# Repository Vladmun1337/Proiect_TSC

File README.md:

# Proiect TSC - Openbook e-book reader

Project link: https://ocw.cs.pub.ro/courses/tsc/proiect2025

## Introduction

For this project, I have implemented an open source e-book reader using ***Autodesk Fusion360***.
The architecture is based on an ESP32-C6 low power microcontroller (+ Wi-Fi & Bluetooth).

The display is using e-paper ink. The project supports micro SD reading through the specialized
interface and USB type C charging for a Polymer Lithium-Ion battery, prioritizing performance
and efficient power consumption.

## Diagram

## Contents

```
- hardware      -> .brd and .sch files of the board
- mechanical    -> .zip files of project's 3D models (standard and exploded view)
- Manufacturing -> Bill of Materials (BOM), Pick and Place (PnP), Gerber files (.zip)
- images        -> Snapshots of project
- LICENSE
- README.md
```

## Implementation & Workflow

1. **Implementation of the schematic**: The deskassistant library, offered by the lecture, was used. All components placed, linked and tagged
   for easier workflow in the PCB part.
2. **PCB**: Board was trimmed to fit specifications and accomodate busses. Components were then placed, respecting the DRC constraints file and routed
accordingly. Power(0.3mm) and data(0.15mm) lines were routed with different gauges and power routing was done mostly on top layer.
3. **3D Modelling**: All components were researched online and their specific 3D model was imported in the library. For a better grasp of the components used,
check BOM below. After the PCB was succesfully modelled, a battery and e-paper display were sketched from scratch.
4. **Fitting everything**: PCB, battery and display were fitted inside the given encasing and given a photoshoot. :-)

## Bill of Materials (with links)

| Name                                             | Link                                                                 | Datasheet                                                            |
|--------------------------------------------------|----------------------------------------------------------------------|----------------------------------------------------------------------|
| 112A-TAAR-R03                                    | [Link](https://store.comet.srl.ro/Catalogue/Product/43497/)         | [Datasheet](https://store.comet.bg/download-file.php?id=27596)      |
| 744043680                                  | [Link](https://eu.mouser.com/ProductDetail/Wurth-Elektronik/744043680?qs=PGXP4M47uW6VkZq%252BkzjrHA%3D%3D) | [Datasheet](https://www.we-online.com/components/products/datasheet/744043680.pdf) |
| BD5229G-TR                                       | [Link](https://componentsearchengine.com/part-view/BD5229G-TR/ROHM%20Semiconductor) | [Datasheet](https://datasheet.datasheetarchive.com/originals/distributors/Datasheets_SAMA/f2b9741ef86007909f138d561a359946.pdf) |
| Button                                           | [Link](https://industry.panasonic.com/global/en/products/control/switch/light-touch/number/evqpuj02k) | [Datasheet](https://industry.panasonic.com/global/en/downloads?tab=catalog&small_g_cd=203&part_no=EVQPUJ02K&q=RVZRUFVKMDJLJTdDMTMlN0MyMDMlN0MzNDU5JTdDMSU3QyU3QzIlN0M%3D) |
| Capacitor                                   | [Link](https://componentsearchengine.com/part-view/CC0402MRX5R5BB106/YAGEO) | [Datasheet](https://componentsearchengine.com/Datasheets/2/CC0402MRX5R5BB106.pdf) |
| CPH3225A                                         | [Link](https://www.snapeda.com/parts/CPH3225A/Seiko+Instruments/view-part/?ref=eda) | [Datasheet](https://www.snapeda.com/parts/CPH3225A/Seiko%20Instruments/datasheet/) |
| DS3231SN RTC                                     | [Link](https://www.snapeda.com/parts/DS3231SN%23/Analog+Devices/view-part/?ref=eda) | [Datasheet](https://www.snapeda.com/parts/DS3231SN%23/Analog%20Devices/datasheet/) |
| ESP32 WROVER 0805 Capacitor                      | [Link](https://ro.mouser.com/ProductDetail/KYOCERA-AVX/SD0805S020S1R0?qs=jCA%252BPfw4LHbpkAoSnwrdjw%3D%3D) | [Datasheet](https://ro.mouser.com/datasheet/2/40/schottky-3165252.pdf) |
| ESP32 WROVER BME680 Sensor                       | [Link](https://www.snapeda.com/parts/BME680/Bosch/view-part/?welcome=home) | [Datasheet](https://www.snapeda.com/parts/BME680/Bosch%20Sensortec/datasheet/) |
| ESP32 WROVER MCP73831           | [Link](https://eu.mouser.com/ProductDetail/Microchip-Technology/MCP73831T-2ACI-OT?qs=yUQqVecv4qvbBQBGbHx0Mw%3D%3D) | [Datasheet](https://eu.mouser.com/datasheet/2/268/MCP73831_Family_Data_Sheet_DS20001984H-3441711.pdf) |
| ESP32 WROVER P-Channel MOSFET                    | [Link](https://componentsearchengine.com/part-view/DMG2305UX-7/Diodes%20Incorporated) | [Datasheet](https://www.diodes.com//assets/Datasheets/DMG2305UX.pdf) |
| ESP32-C6 WROOM-1-N8                              | [Link](https://www.snapeda.com/parts/ESP32-C6-WROOM-1-N8/Espressif+Systems/view-part/?ref=eda) | [Datasheet](https://www.snapeda.com/parts/ESP32-C6-WROOM-1-N8/Espressif%20Systems/datasheet/) |
| ESP32C6 Varistor 1812                            | [Link](https://ro.mouser.com/ProductDetail/EPCOS-TDK/B72520T0350K062?qs=dEfas%2FXlABIszF52uu7vrg%3D%3D) | [Datasheet](https://www.tdk-electronics.tdk.com/inf/75/db/CTVS_14/Surge_protection_series.pdf) |
| FH34SRJ-24S-0.5SH Connector                      | [Link](https://componentsearchengine.com/part-view/FH34SRJ-24S-0.5SH(99)/Hirose) | [Datasheet](https://www.hirose.com/en/product/document?clcode=CL0580-1255-6-99&productname=FH34SRJ-24S-0.5SH(99)&series=FH34SRJ&documenttype=2DDrawing&lang=en&documentid=0000990903) |
| LED 0603                                    | [Link](https://www.snapeda.com/parts/KP-1608SURCK/Kingbright/view-part/?ref=search&t=LED%200603) | [Datasheet](https://www.snapeda.com/parts/KP-1608SURCK/Kingbright/datasheet/) |
| LTSPICE Resistor 0402                            | [Link](https://componentsearchengine.com/part-view/R0402%201%25%20100%20K%20(RC0402FR-07100KL)/YAGEO) | [Datasheet](https://www.yageo.com/upload/media/product/products/datasheet/rchip/PYu-RC_Group_51_RoHS_L_12.pdf) |
| MAX17048G+T10                 | [Link](https://www.snapeda.com/parts/MAX17048G+T10/Analog+Devices/view-part/?ref=eda) | [Datasheet](https://www.snapeda.com/parts/MAX17048G+T10/Analog%20Devices/datasheet/) |
| MBR0530 Schottky                           | [Link](https://www.snapeda.com/parts/MBR0530/Onsemi/view-part/?ref=eda) | [Datasheet](https://www.snapeda.com/parts/MBR0530/ON%20Semiconductor/datasheet/) |
| PGB1010603MR                            | [Link](https://www.snapeda.com/parts/PGB1010603MR/Littelfuse/view-part/?ref=eda) | [Datasheet](https://www.snapeda.com/parts/PGB1010603MR/Littelfuse%20Inc./datasheet/) |
| QWIIC Connector                                  | [Link](https://eu.mouser.com/ProductDetail/Adafruit/4208?qs=PzGy0jfpSMtbScLbr0L5dw%3D%3D) | [Datasheet](https://www.youtube.com/watch?v=dQw4w9WgXcQ) |
| RCL CPOL 3528                                    | [Link](https://www.snapeda.com/parts/TAJB475K025RNJ/AVX/view-part/?ref=dk&t=capacitor%203528&con_ref=None) | [Datasheet](https://s3.amazonaws.com/snapeda/datasheet/TAJB475K025RNJ_AVX.pdf) |
| SI1308EDL-T1-GE3 MOSFET                          | [Link](https://www.snapeda.com/parts/SI1308EDL-T1-GE3/Vishay+Siliconix/view-part/?ref=eda) | [Datasheet](https://www.youtube.com/watch?v=dQw4w9WgXcQ) |
| SJ                                               | [Link](https://grabcad.com/library/solder-jumpers-1)                 | [Datasheet](https://www.youtube.com/watch?v=dQw4w9WgXcQ)             |
| TPTP20R                                          | [Link](https://easyeda.com/component/7524403feb2642ac9f9f26dfb93ceacf) | [Datasheet](https://easyeda.com/component/7524403feb2642ac9f9f26dfb93ceacf) |
| USB4110-GF-A USB                             | [Link](https://componentsearchengine.com/part-view/USB4110-GF-A/GCT%20(GLOBAL%20CONNECTOR%20TECHNOLOGY)) | [Datasheet](https://gct.co/files/drawings/usb4110.pdf)             |
| USBLC6-2SC6Y USB                | [Link](https://www.snapeda.com/parts/USBLC6-2SC6Y/STMicroelectronics/view-part/?ref=eda) | [Datasheet](https://www.snapeda.com/parts/USBLC6-2SC6Y/STMicroelectronics/datasheet/) |
| W25Q512JVEIQ Flash                      | [Link](https://www.snapeda.com/parts/W25Q512JVEIQ/Winbond+Electronics/view-part/?ref=eda) | [Datasheet](https://www.snapeda.com/parts/W25Q512JVEIQ/Winbond%20Electronics/datasheet/) |
| XC6220A331MR-G Voltage Regulator                 | [Link](https://componentsearchengine.com/part-view/XC6220A331MR-G/Torex) | [Datasheet](https://product.torexsemi.com/system/files/series/xc6220.pdf) |

## ESP32-C6 Pinout

An overview of how the ESP32-C6 pins are assigned within the system, grouped by function.

### Power
- **3V3 (Pin 2 & Top Right):** 3.3V supply for ESP32 and peripherals.
- **GND (Bottom Right):** Common ground.

### Boot and Reset
- **GPIO8 (Pin 15):** Boot mode selection, pulled low via 10KΩ.
- **RESET (Pin 3):** Manual reset input.

### SPI (E-Paper Display, SD Card, Flash)
- **MISO (Pin 27)**
- **MOSI (Pin 10)**
- **SCK (Pin 7)**
- **SS_SD (Pin 4):** Chip Select for SD card or other SPI device.
- **EPD_CS (Pin 11):** Chip Select for E-Paper Display.
- **FLASH_CS (Pin 12):** Chip Select for NOR Flash.

### E-Paper Display Control
- **EPD_BUSY (Pin 26)**
- **EPD_DC (Pin 5)**
- **EPD_RST (Pin 21)**
- **EPD_3V3_C (Pin 19):** Likely power enable/control.

### I2C (RTC & Sensors)
- **SDA (Pin 20)**
- **SCL (Pin 21)**
- **I2C_PW (Pin 18):** Power enable for I2C devices.
- **INT_RTC (Pin 8):** RTC interrupt.
- **RTC_RST (Pin 16)**

### USB
- **USB_D- (Pin 13)**
- **USB_D+ (Pin 14)**

### UART
- **TX (Pin 25)**
- **RX (Pin 24)**

### Other GPIO
- **IO_CHANGE (Pin 23):** Interrupt or status input/output.

## Total Power Consumption Overview

In a typical operating scenario—where the ESP32-C6 remains active with Wi-Fi enabled, the e-paper display refreshes every 10 seconds, and the BME688 sensor continuously collects environmental data—the estimated current draw for the system is as follows:

| Component                          | Estimated Consumption (mA) |
|-----------------------------------|-----------------------------|
| ESP32-C6 (Wi-Fi enabled)          | 200 mA                      |
| E-Paper Display (during update)   | 40 mA                       |
| BME688 Sensor (continuous use)    | 2 mA                        |
| Real-Time Clock (RTC) Module      | 2 mA                        |
| SD Card (active use)              | 12 mA                       |
| External NOR Flash Memory         | 25 mA                       |

### Typical Total Current Draw

**Total: 281 mA**

This estimate represents a high-activity configuration. In lower-power modes (e.g., sleep or deep sleep), consumption can be significantly reduced.

## Conclusions

This project was very exciting for me. A lot of difficulties came from me having little to no prior experience with the autodesk suite, but everything sorted
itself out. I feel that I could get a good grasp of what working in the hardware and product industry means and am open to work on more other such projects! :-)

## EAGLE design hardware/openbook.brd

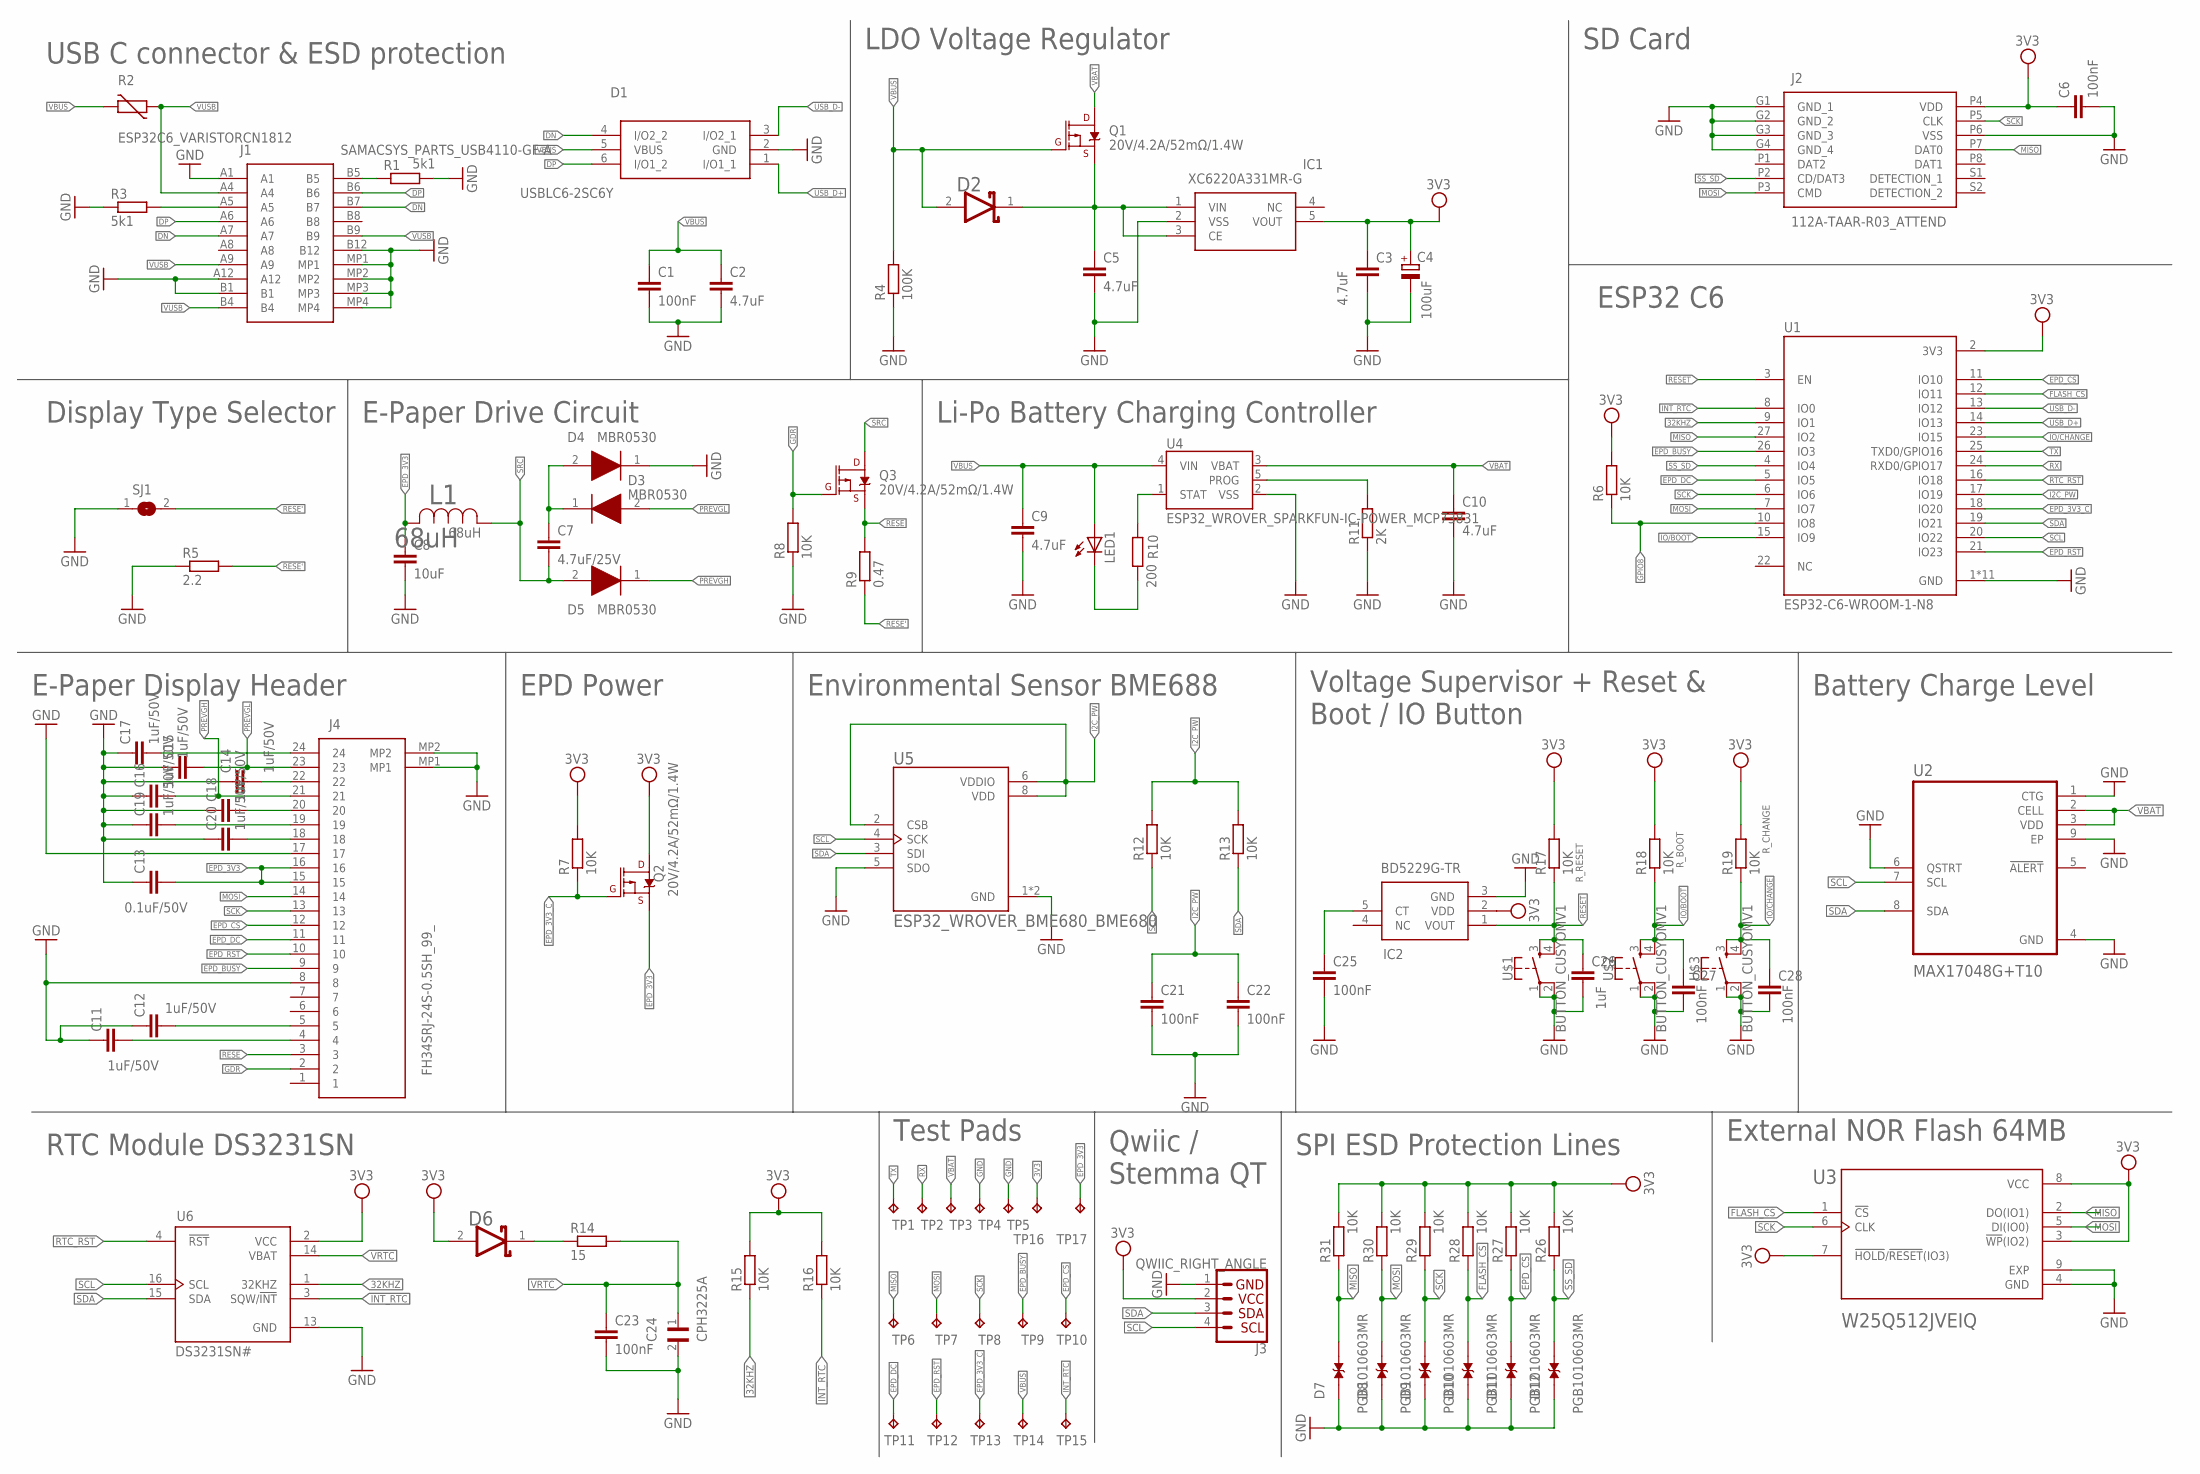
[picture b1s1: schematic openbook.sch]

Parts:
C1, C6, C21, C22, C23, C25, C27, C28: 100nF; EAGLE-LTSPICE_C0402
C2, C3, C5, C9, C10: 4.7uF; EAGLE-LTSPICE_C0402
C4: 100uF; RCL_CT3528
C7: 4.7uF/25V; EAGLE-LTSPICE_C0402
C8: 10uF; EAGLE-LTSPICE_C0402
C11, C12, C14, C15, C16, C17, C18, C19, C20: 1uF/50V; EAGLE-LTSPICE_C0402
C13: 0.1uF/50V; EAGLE-LTSPICE_C0402
C24: CPH3225A; CAPCP3225X100N
C26: 1uF; EAGLE-LTSPICE_C0402
D1: USBLC6-2SC6Y; SOT95P280X145-6N
D2, D6: ESP32_WROVER_AVX---SD0805S020S1R0_AVX_SD0805S020S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; ESP32_WROVER_AVX---SD0805S020S1R0_AVX_SD0805S020S1R0_0
D3, D4, D5: MBR0530; SOD3716X135N
D7, D8, D9, D10, D11, D12: PGB1010603MR; DIOC1608X36N
IC1: XC6220A331MR-G; SOT95P280X120-5N
IC2: BD5229G-TR; SOT95P280X125-5N
J1: SAMACSYS_PARTS_USB4110-GF-A; SAMACSYS_PARTS_USB4110GFA
J2: 112A-TAAR-R03_ATTEND; 112ATAARR03ATTEND
J3: QWIIC_RIGHT_ANGLE; JST04_1MM_RA
J4: FH34SRJ-24S-0.5SH_99_; FH34SRJ24S05SH99
L1: 68uH; IND_4828-WE-TPC_WRE
LED1: ADAFRUIT_LEDCHIP-LED0603; ADAFRUIT_CHIP-LED0603
Q1, Q2, Q3: 20V/4.2A/52mΩ/1.4W; ESP32_WROVER_SPARKFUN-DISCRETESEMI_SOT23-3
R1, R3: 5k1; ESP32_WROVER_EAGLE-LTSPICE_R0402
R2: ESP32C6_VARISTORCN1812; ESP32C6_VARISTOR_CT/CN1812
R4: 100K; ESP32_WROVER_EAGLE-LTSPICE_R0402
R5: 2.2; ESP32_WROVER_EAGLE-LTSPICE_R0402
R6, R7, R8, R12, R13, R15, R16, R17, R18, R19, R26, R27, R28, R29, R30, R31: 10K; ESP32_WROVER_EAGLE-LTSPICE_R0402
R9: 0.47; ESP32_WROVER_EAGLE-LTSPICE_R0402
R10: 200; ESP32_WROVER_EAGLE-LTSPICE_R0402
R11: 2K; ESP32_WROVER_EAGLE-LTSPICE_R0402
R14: 15; ESP32_WROVER_EAGLE-LTSPICE_R0402
SJ1: SJ
TP1, TP2, TP3, TP4, TP5, TP6, TP7, TP8, TP9, TP10, TP11, TP12, TP13, TP14, TP15, TP16, TP17: TPTP20R; TP20R
U1: ESP32-C6-WROOM-1-N8; XCVR_ESP32-C6-WROOM-1-N8
U2: MAX17048G+T10; SON50P200X200X80-9N
U3: W25Q512JVEIQ; SON127P600X800X80-9N
U4: ESP32_WROVER_SPARKFUN-IC-POWER_MCP73831; ESP32_WROVER_SPARKFUN-IC-POWER_SOT23-5
U5: ESP32_WROVER_BME680_BME680; ESP32_WROVER_BME680_PSON80P300X300X100-8N
U6: DS3231SN#; SOIC127P1032X265-16N
U$1, U$2, U$3: BUTTON_CUSYOMV1; MYBUTTON

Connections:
3V3: C3.1, C4.+, C6.1, D6.2 (ANODE), IC1.5 (VOUT), IC2.2 (VDD), J2.P4 (VDD), J3.2, Q2.3 (D), R6.2, R7.2, R15.2, R16.2, R17.2, R18.2, R19.2, R26.2, R27.2, R28.2, R29.2, R30.2, R31.2, TP16.TP, U1.2 (3V3), U3.3 (!WP!(IO2)), U3.7 (!HOLD!/!RESET!(IO3)), U3.8 (VCC), U6.2 (VCC)
32KHZ: R15.1, U1.9 (IO1), U6.1 (32KHZ)
DN: D1.4 (I/O2_2), J1.A7, J1.B7
DP: D1.6 (I/O1_2), J1.A6, J1.B6
EPD_3V3: C8.1, C13.2, J4.15, J4.16, L1.2, Q2.2 (S), TP17.TP
EPD_3V3_C: Q2.1 (G), R7.1, TP13.TP, U1.18 (IO20)
EPD_BUSY: J4.9, TP9.TP, U1.26 (IO3)
EPD_CS: D11.2, J4.12, R27.1, TP10.TP, U1.11 (IO10)
EPD_DC: J4.11, TP11.TP, U1.5 (IO5)
EPD_RST: J4.10, TP12.TP, U1.21 (IO23)
FLASH_CS: D10.2, R28.1, U1.12 (IO11), U3.1 (!CS)
GDR: J4.2, Q3.1 (G), R8.2
GND: C1.2, C2.2, C3.2, C4.-, C5.2, C6.2, C8.2, C9.2, C10.2, C11.1, C12.1, C13.1, C14.1, C15.1, C16.1, C17.1, C18.1, C19.1, C20.1, C21.2, C22.2, C23.2, C24.2, C25.2, C26.2, C27.2, C28.2, D1.2 (GND), D4.1 (K), D7.1, D8.1, D9.1, D10.1, D11.1, D12.1, IC1.2 (VSS), IC2.3 (GND), J1.A1, J1.A12, J1.B1, J1.B12, J1.MP1, J1.MP2, J1.MP3, J1.MP4, J2.G1 (GND_1), J2.G2 (GND_2), J2.G3 (GND_3), J2.G4 (GND_4), J2.P6 (VSS), J3.1, J4.8, J4.17, J4.MP1, J4.MP2, R1.2, R3.1, R4.1, R5.1, R8.1, R11.1, SJ1.1, TP4.TP, TP5.TP, U1.1 (GND), U1.28 (GND), U1.29_1 (GND), U1.29_2 (GND), U1.29_3 (GND), U1.29_4 (GND), U1.29_5 (GND), U1.29_6 (GND), U1.29_7 (GND), U1.29_8 (GND), U1.29_9 (GND), U2.1 (CTG), U2.4 (GND), U2.6 (QSTRT), U2.9 (EP), U3.4 (GND), U3.9 (EXP), U4.2 (VSS), U5.1 (GND), U5.5 (SDO), U5.7 (GND), U6.13 (GND), U$1.1, U$1.2, U$2.1, U$2.2, U$3.1, U$3.2
GPIO8: R6.1, U1.10 (IO8)
I2C_PW: C21.1, C22.1, R12.2, R13.2, U1.17 (IO19), U5.2 (CSB), U5.6 (VDDIO), U5.8 (VDD)
INT_RTC: R16.1, TP15.TP, U1.8 (IO0), U6.3 (SQW/!INT)
IO/BOOT: C27.1, R18.1, U1.15 (IO9), U$2.3, U$2.4
IO/CHANGE: C28.1, R19.1, U1.23 (IO15), U$3.3, U$3.4
MISO: D7.2, J2.P7 (DAT0), R31.1, TP6.TP, U1.27 (IO2), U3.2 (DO(IO1))
MOSI: D8.2, J2.P3 (CMD), J4.14, R30.1, TP7.TP, U1.7 (IO7), U3.5 (DI(IO0))
unnamed: D6.1 (CATHODE), R14.1
unnamed: J1.B5, R1.1
unnamed: J1.A5, R3.2
unnamed: C5.1, D2.1 (CATHODE), IC1.1 (VIN), IC1.3 (CE), Q1.2 (S)
unnamed: C7.1, D3.1 (K), D4.2 (A)
unnamed: LED1.C, R10.1
unnamed: R10.2, U4.1 (STAT)
unnamed: R11.2, U4.5 (PROG)
unnamed: C11.2, J4.4
unnamed: C12.2, J4.5
unnamed: C20.2, J4.18
unnamed: C19.2, J4.19
unnamed: C18.2, J4.20
unnamed: C14.2, J4.22
unnamed: C17.2, J4.24
unnamed: C25.1, IC2.5 (CT)
PREVGH: C16.2, D5.1 (K), J4.21
PREVGL: C15.2, D3.2 (A), J4.23
RESE: J4.3, Q3.2 (S), R9.2
RESE': R5.2, R9.1, SJ1.2
RESET: C26.1, IC2.1 (VOUT), R17.1, U1.3 (EN), U$1.3, U$1.4
RTC_RST: U1.16 (IO18), U6.4 (!RST)
RX: TP2.TP, U1.24 (RXD0/GPIO17)
SCK: D9.2, J2.P5 (CLK), J4.13, R29.1, TP8.TP, U1.6 (IO6), U3.6 (CLK)
SCL: J3.4, R12.1, U1.20 (IO22), U2.7 (SCL), U5.4 (SCK), U6.16 (SCL)
SDA: J3.3, R13.1, U1.19 (IO21), U2.8 (SDA), U5.3 (SDI), U6.15 (SDA)
SRC: C7.2, D5.2 (A), L1.1, Q3.3 (D)
SS_SD: D12.2, J2.P2 (CD/DAT3), R26.1, U1.4 (IO4)
TX: TP1.TP, U1.25 (TXD0/GPIO16)
USB_D+: D1.1 (I/O1_1), U1.14 (IO13)
USB_D-: D1.3 (I/O2_1), U1.13 (IO12)
VBAT: C10.1, Q1.3 (D), TP3.TP, U2.2 (CELL), U2.3 (VDD), U4.3 (VBAT)
VBUS: C1.1, C2.1, C9.1, D1.5 (VBUS), D2.2 (ANODE), LED1.A, Q1.1 (G), R2.2, R4.2, TP14.TP, U4.4 (VIN)
VRTC: C23.1, C24.1, R14.2, U6.14 (VBAT)
VUSB: J1.A4, J1.A9, J1.B4, J1.B9, R2.1

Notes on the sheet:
USB C connector & ESD protection
LDO Voltage Regulator
SD Card
Display Type Selector
E-Paper Drive Circuit
Li-Po Battery Charging Controller
ESP32 C6
E-Paper Display Header
RTC Module DS3231SN
EPD Power
Environmental Sensor BME688
Test Pads
Qwiic / Stemma QT
Voltage Supervisor + Reset & Boot / IO Button
SPI ESD Protection Lines
Battery Charge Level
External NOR Flash 64MB
68uH
R_RESET
R_BOOT
R_CHANGE

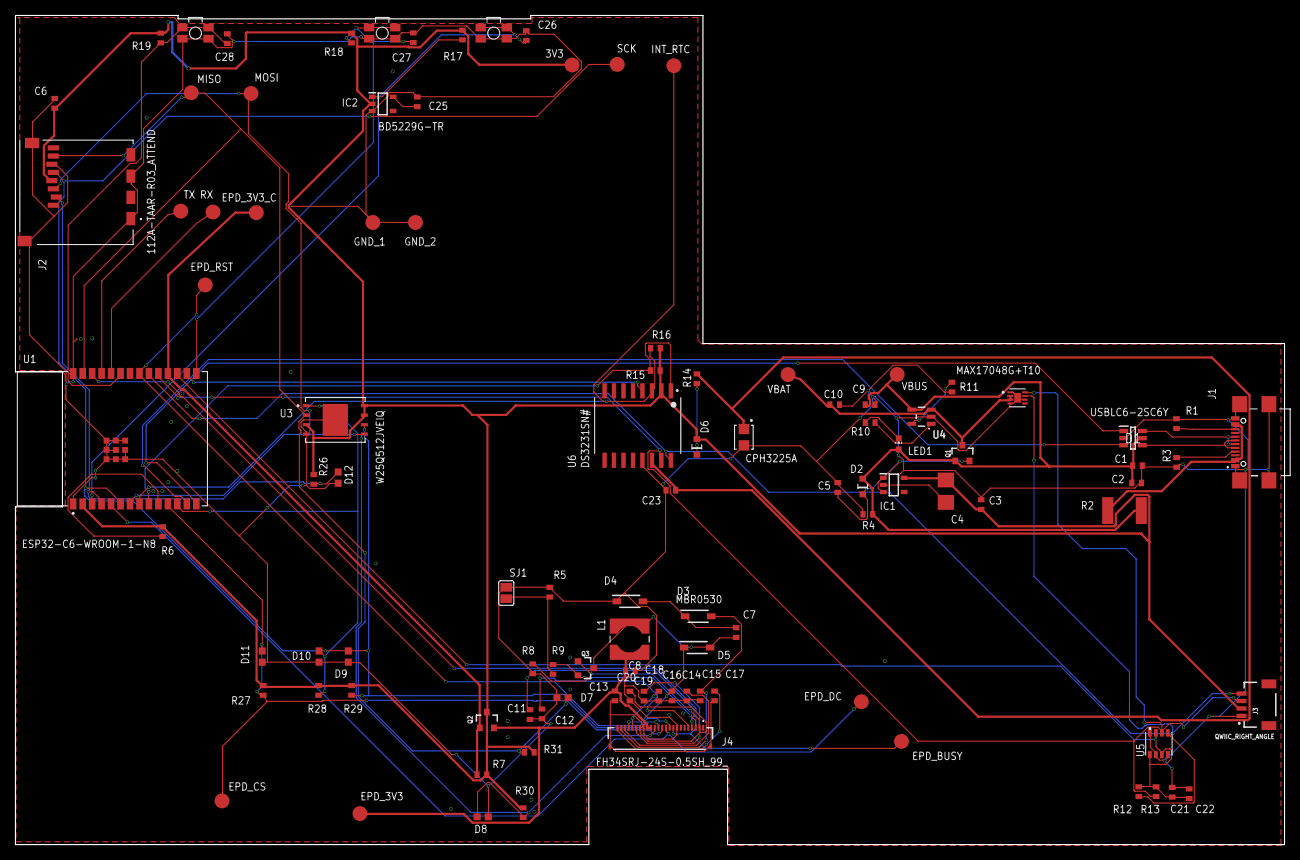
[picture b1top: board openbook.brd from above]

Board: 2 copper layers, 170.2 x 111.2 mm, 103 parts (0 on the bottom side), 55 nets.

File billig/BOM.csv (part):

Qty,Value,Device,Package,Parts,Description,ARROW_PART_NUMBER,ARROW_PRICE-STOCK,AVAILABILITY,CENTROID_NOT_SPECIFIED,CHECK_PRICES,COPYRIGHT,DATASHEET,DESCRIPTION,DIGIKEY_DESCRIPTION,DIGIKEY_PART_NUMBER,HEIGHT,LEAD_FREE,MANUFACTURER_NAME,MANUFACTURER_PART_NUMBER,MF,MFR_NAME,MOUSER_PART_NUMBER,MOUSER_PRICE-STOCK,MOUSER_TESTING_PART_NUMBER,MOUSER_TESTING_PRICE-STOCK,MP,MPN,PACKAGE,POPULARITY,PREFIX,PRICE,PROD_ID,PURCHASE-URL,ROHS,SNAPEDA_LINK,SPICEMODEL,SPICEPREFIX,TEMPERATURE_RANGE_HIGH,TEMPERATURE_RANGE_LOW,TP_SIGNAL_NAME,VALUE
1,,ADAFRUIT_LEDCHIP-LED0603,ADAFRUIT_CHIP-LED0603,LED1,LED,,,,,,,,,,,,,,,,,,,,,,,,,,,,,,,,,,,,
1,,SJ,SJ,SJ1,"SMD solder JUMPER",,,,,,,,,,,,,,,,,,,,,,,,3,,,,,,,,,,,,
1,0.1uF/50V,EAGLE-LTSPICE_CC0402,EAGLE-LTSPICE_C0402,C13,"CAPACITOR, European symbol",,,,,,,,,,,,,,,,,,,,,,,,,,,,,,,NONE,C,,,,
1,0.47,ESP32_WROVER_EAGLE-LTSPICE_RR0402,ESP32_WROVER_EAGLE-LTSPICE_R0402,R9,"RESISTOR, European symbol",,,,,,,,,,,,,,,,,,,,,,,,,,,,,,,NONE,R,,,,
1,100K,ESP32_WROVER_EAGLE-LTSPICE_RR0402,ESP32_WROVER_EAGLE-LTSPICE_R0402,R4,"RESISTOR, European symbol",,,,,,,,,,,,,,,,,,,,,,,,,,,,,,,NONE,R,,,,
8,100nF,EAGLE-LTSPICE_CC0402,EAGLE-LTSPICE_C0402,"C1, C6, C21, C22, C23, C25, C27, C28","CAPACITOR, European symbol",,,,,,,,,,,,,,,,,,,,,,,,,,,,,,,NONE,C,,,,
1,100uF,RCL_CPOL-EUCT3528,RCL_CT3528,C4,"POLARIZED CAPACITOR, European symbol",,,,,,,,,,,,,,,,,,,,,,,,0,,,,,,,,C,,,,
16,10K,ESP32_WROVER_EAGLE-LTSPICE_RR0402,ESP32_WROVER_EAGLE-LTSPICE_R0402,"R6, R7, R8, R12, R13, R15, R16, R17, R18, R19, R26, R27, R28, R29, R30, R31","RESISTOR, European symbol",,,,,,,,,,,,,,,,,,,,,,,,,,,,,,,NONE,R,,,,
1,10uF,EAGLE-LTSPICE_CC0402,EAGLE-LTSPICE_C0402,C8,"CAPACITOR, European symbol",,,,,,,,,,,,,,,,,,,,,,,,,,,,,,,NONE,C,,,,
1,112A-TAAR-R03_ATTEND,112A-TAAR-R03_ATTEND,112ATAARR03ATTEND,J2,"Micro SD Card Socket, Push-Push Type, Top Mount, SMT, H=1.83mm, 10u",,,,,,,,"Micro SD Card Socket"," Push-Push Type"," Top Mount"," SMT"," H=1.83mm"," 10u",,,1.9mm,,ATTEND,"112A-TAAR-R03 ATTEND",,,,,,,,,,,,,,,,,
1,15,ESP32_WROVER_EAGLE-LTSPICE_RR0402,ESP32_WROVER_EAGLE-LTSPICE_R0402,R14,"RESISTOR, European symbol",,,,,,,,,,,,,,,,,,,,,,,,,,,,,,,NONE,R,,,,
1,1uF,EAGLE-LTSPICE_CC0402,EAGLE-LTSPICE_C0402,C26,"CAPACITOR, European symbol",,,,,,,,,,,,,,,,,,,,,,,,,,,,,,,NONE,C,,,,
9,1uF/50V,EAGLE-LTSPICE_CC0402,EAGLE-LTSPICE_C0402,"C11, C12, C14, C15, C16, C17, C18, C19, C20","CAPACITOR, European symbol",,,,,,,,,,,,,,,,,,,,,,,,,,,,,,,NONE,C,,,,
1,2.2,ESP32_WROVER_EAGLE-LTSPICE_RR0402,ESP32_WROVER_EAGLE-LTSPICE_R0402,R5,"RESISTOR, European symbol",,,,,,,,,,,,,,,,,,,,,,,,,,,,,,,NONE,R,,,,
1,200,ESP32_WROVER_EAGLE-LTSPICE_RR0402,ESP32_WROVER_EAGLE-LTSPICE_R0402,R10,"RESISTOR, European symbol",,,,,,,,,,,,,,,,,,,,,,,,,,,,,,,NONE,R,,,,
3,20V/4.2A/52mO/1.4W,ESP32_WROVER_SPARKFUN-DISCRETESEMI_MOSFET_PCH-DMG2305UX-7,ESP32_WROVER_SPARKFUN-DISCRETESEMI_SOT23-3,"Q1, Q2, Q3","P-channel MOSFETs",,,,,,,,,,,,,,,,,,,,,,,,,,,TRAN-14388,,,,,,,,,20V/4.2A/52mO/1.4W
1,2K,ESP32_WROVER_EAGLE-LTSPICE_RR0402,ESP32_WROVER_EAGLE-LTSPICE_R0402,R11,"RESISTOR, European symbol",,,,,,,,,,,,,,,,,,,,,,,,,,,,,,,NONE,R,,,,
5,4.7uF,EAGLE-LTSPICE_CC0402,EAGLE-LTSPICE_C0402,"C2, C3, C5, C9, C10","CAPACITOR, European symbol",,,,,,,,,,,,,,,,,,,,,,,,,,,,,,,NONE,C,,,,
1,4.7uF/25V,EAGLE-LTSPICE_CC0402,EAGLE-LTSPICE_C0402,C7,"CAPACITOR, European symbol",,,,,,,,,,,,,,,,,,,,,,,,,,,,,,,NONE,C,,,,
2,5k1,ESP32_WROVER_EAGLE-LTSPICE_RR0402,ESP32_WROVER_EAGLE-LTSPICE_R0402,"R1, R3","RESISTOR, European symbol",,,,,,,,,,,,,,,,,,,,,,,,,,,,,,,NONE,R,,,,
1,68uH,744043680IND_4828-WE-TPC_WRE,IND_4828-WE-TPC_WRE,L1,,,,,,,"Copyright (C) 2024 Ultra Librarian. All rights reserved.",,,,,,,,744043680,,"Wurth Electronics",,,,,,,,,,,,,,,,,,,,
1,BD5229G-TR,BD5229G-TR,SOT95P280X125-5N,IC2,"Voltage Detector with Adjustable Delay Time: CMOS processes are utilized to develop high precision, low current consumption CMOS reset ICs that allow arbitrary setting of the delay time. The extensive lineup includes both Nch Open Drain and CMOS output types in a wide range of detection voltages (from 2.3V to 6.0V, in 0.1V steps), enabling selection of the ideal solution based on customer requirements. In addition, the entire series is of course both lead-free and RoHS-compliant.",,,,,,,,"Voltage Detector with Adjustable Delay Time: CMOS processes are utilized to develop high precision"," low current consumption CMOS reset ICs that allow arbitrary setting of the delay time. The extensive lineup includes both Nch Open Drain and CMOS output types in a wide range of detection voltages (from 2.3V to 6.0V"," in 0.1V steps)"," enabling selection of the ideal solution based on customer requirements. In addition"," the entire series is of course both lead-free and RoHS-compliant.",,,1.25mm,,"ROHM Semiconductor",BD5229G-TR,,,755-BD5229G-TR,https://www.mouser.co.uk/ProductDetail/ROHM-Semiconductor/BD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,,,,,,,,,,,,,,
3,BUTTON_CUSYOMV1,BUTTON_CUSYOMV1,MYBUTTON,"U$1, U$2, U$3",,,,,,,,,,,,,,,,,,,,,,,,,,,,,,,,,,,,,
1,CPH3225A,CPH3225A,CAPCP3225X100N,C24,"Cap 0.011F 3.3V 1210 Flat Check availability",,,"Not in stock",,https://www.snapeda.com/parts/CPH3225A/Seiko+Instruments/vie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,,," 11 mF (EDLC) Supercapacitor 3.3 V 1210 (3225 Metric) - - ",,,,,,,"Seiko Instruments",,,,,,CPH3225A,,"1210 Seiko",,,None,,"https://www.snapeda.com/api/url_track_click_mouser/?unipart_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 Instruments&part_name=CPH3225A&search_term=None",,https://www.snapeda.com/parts/CPH3225A/Seiko+Instruments/vie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,,,,,,
1,DS3231SN#,DS3231SN#,SOIC127P1032X265-16N,U6,"Real Time Clock Serial 16-Pin SOIC W T/R     Check availability",,,"In Stock",,https://www.snapeda.com/parts/DS3231SN%23/Analog+Devices/vie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,,," Extremely Accurate I²C-Integrated RTC/TCXO/Crystal ",,,,,,,"Analog Devices",,,,,,DS3231SN#,,"SOIC-16 Maxim",,,None,,"https://www.snapeda.com/api/url_track_click_mouser/?unipart_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 Devices&part_name=DS3231SN#&search_term=None",,https://www.snapeda.com/parts/DS3231SN%23/Analog+Devices/vie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,,,,,,
1,ESP32-C6-WROOM-1-N8,ESP32-C6-WROOM-1-N8,XCVR_ESP32-C6-WROOM-1-N8,U1,"Check availability",,,"In Stock",,https://www.snapeda.com/parts/ESP32-C6-WROOM-1-N8/Espressif+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,,," Multiprotocol Modules ESP32-C6 module"," Wi-Fi 6 in 2.4 GHz band"," Bluetooth 5"," Zigbee 3.0 and Thread. ESP34-WROOM Compatible - ENGINEERING SAMPLE ",,,,,,,"Espressif Systems",,,,,,ESP32-C6-WROOM-1-N8,,None,,,None,,,,https://www.snapeda.com/parts/ESP32-C6-WROOM-1-N8/Espressif+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,,,
1,ESP32C6_VARISTORCN1812,ESP32C6_VARISTORCN1812,ESP32C6_VARISTOR_CT/CN1812,R2,VARISTOR,,,,,,,,,,,,,,,,,,,,,,,,0,,,,,,,,,,,,
2,ESP32_WROVER_AVX---SD0805S020S1R0_AVX_SD0805S020S1R0_0_0AVX_SD0805S020S1R0_0_0,ESP32_WROVER_AVX---SD0805S020S1R0_AVX_SD0805S020S1R0_0_0AVX_SD0805S020S1R0_0_0,ESP32_WROVER_AVX---SD0805S020S1R0_AVX_SD0805S020S1R0_0,"D2, D6","Schottky Barrier Rectifier Diode",,,,No,,,http://datasheets.avx.com/schottky.pdf,,"DIODE SCHOTTKY 20V 1A 0805",478-7800-1-ND,,yes,,,AVX,,581-SD0805S020S1R0,,,,,,"0805 (2012 metric)",,D,,,,yes,,,,+125°C,-55°C,,
1,ESP32_WROVER_BME680_BME680,ESP32_WROVER_BME680_BME680,ESP32_WROVER_BME680_PSON80P300X300X100-8N,U5,"Integrated Environmental Unit",,,Unavailable,,,,," Integrated Environmental Unit ",,,,,,,"Bosch Sensortec",,,,,,BME680,,"LGA-8 Bosch Tools",,,None,,,,,,,,,,
1,ESP32_WROVER_SPARKFUN-IC-POWER_MCP73831,ESP32_WROVER_SPARKFUN-IC-POWER_MCP73831,ESP32_WROVER_SPARKFUN-IC-POWER_SOT23-5,U4,"MCP73831T Li-Ion, Li-Pol Controller",,,,,,,,,,,,,,,,,,,,,,,,,,,IC-09995,,,,,,,,,
1,FH34SRJ-24S-0.5SH_99_,FH34SRJ-24S-0.5SH_99_,FH34SRJ24S05SH99,J4," (0.50mm) Surface Mount, Right Angle",,,,,,,,"24 Position FFC"," FPC Connector Contacts"," (0.50mm) Surface Mount"," Right Angle",,,1.1mm,,Hirose,FH34SRJ-24S-0.5SH(99),,,798-FH34SRJ24S05SH99,https://www.mouser.co.uk/ProductDetail/Hirose-Connector/FH34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,,,,,,,,,,,,,,,
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
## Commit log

2025-04-06 Add images
2025-04-06 Add hardware files
2025-04-06 Add mechanical file zips
2025-04-06 Add billing and gerber
2025-04-06 Add billing files
2025-04-06 Add manufacturing
2025-04-06 Add diagram
2025-04-10 Fixed schematic issues
2025-04-10 Updated button positions, wire angles, allignment
2025-04-11 Fixed ground plane and silkscreen issues
2025-04-11 Modify layer of component names
2025-04-11 Update board render
2025-04-11 Update images
2025-04-11 Add board image
2025-04-11 Update .step files
2025-04-11 Update product render

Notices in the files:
parts and their libraries:
COPYRIGHT: Copyright (C) 2024 Ultra Librarian. All rights reserved.
